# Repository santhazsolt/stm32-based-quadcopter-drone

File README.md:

# STM32-Based Quadcopter Flight Controller

**A custom embedded flight controller built around the STM32F411 microcontroller, an ICM-20948 inertial measurement unit, and a custom-designed PCB.**

This project focuses on the design and development of a quadcopter flight controller, combining embedded C firmware, sensor interfacing, control-system development, power electronics, and printed circuit board (PCB) design.

The goal is to develop a custom hardware and firmware platform capable of reading inertial sensor data, estimating the drone's attitude, processing pilot commands, and controlling four electronic speed controllers (ESCs). The project is also intended to serve as a foundation for future autonomous flight and precision agriculture applications.

**Repository:** [stm32-based-quadcopter-drone](https://github.com/santhazsolt/stm32-based-quadcopter-drone)

---

## Table of Contents

- [Project Overview](#project-overview)
- [Project Objectives](#project-objectives)
- [System Architecture](#system-architecture)
- [Hardware Design](#hardware-design)
- [Power Management](#power-management)
- [Firmware Architecture](#firmware-architecture)
- [Flight Control Fundamentals](#flight-control-fundamentals)
- [Communication Interfaces](#communication-interfaces)
- [Development Tools](#development-tools)
- [Repository Structure](#repository-structure)
- [Development Workflow](#development-workflow)
- [Hardware Bring-Up and Testing](#hardware-bring-up-and-testing)
- [Current Development Status](#current-development-status)
- [Planned Improvements](#planned-improvements)
- [Safety Considerations](#safety-considerations)
- [Learning Outcomes](#learning-outcomes)
- [References](#references)
- [License](#license)

---

## Project Overview

Commercial flight controllers typically integrate a microcontroller, inertial sensors, power regulation, communication interfaces, and motor-control outputs on a single PCB.

This project explores how those components can be designed and integrated into a custom embedded system.

The hardware is built around the **STM32F411CEU6**, an ARM Cortex-M4 microcontroller with an FPU, hardware timers, SPI, UART, ADC, and other peripherals suitable for real-time embedded applications.

The controller interfaces with an **ICM-20948 9-axis IMU**, which combines a 3-axis accelerometer, a 3-axis gyroscope, and a 3-axis magnetometer. The sensor provides measurements that can be used for attitude estimation and flight stabilization.

The project covers two interconnected areas:

- **Hardware:** Schematic design, component selection, PCB layout, power distribution, signal interfacing, and hardware debugging.
- **Firmware:** Peripheral configuration, sensor drivers, inertial data processing, attitude estimation, control algorithms, and ESC signal generation.

The long-term objective is to develop a functional flight-control platform that can be extended with GPS navigation, autonomous flight, and aerial crop-monitoring capabilities.

## Project Objectives

The primary objectives are to:

1. Design a custom flight-controller PCB around the STM32F411.
2. Integrate an inertial measurement unit using SPI communication.
3. Develop embedded C firmware for sensor acquisition and peripheral control.
4. Establish the software architecture for attitude estimation and PID-based stabilization.
5. Generate control signals for four ESCs using STM32 hardware timers.
6. Integrate a radio-control receiver for manual pilot input.
7. Design a power architecture suitable for operation from a LiPo battery.
8. Establish a repeatable hardware bring-up and debugging procedure.
9. Build a modular platform that can support future autonomous navigation and precision agriculture applications.

---

## System Architecture

The flight controller is designed as a real-time embedded system. Its main responsibility is to process sensor measurements and pilot commands, calculate the required control response, and generate motor outputs.

```mermaid
flowchart TD
    BAT[LiPo Battery] --> PWR[Power Management]
    PWR --> MCU[STM32F411]
    PWR --> IMU[ICM-20948 IMU]
    RC[RC Receiver] --> MCU
    IMU -->|SPI| MCU
    MCU -->|PWM or supported ESC protocol| ESC[Four ESCs]
    ESC --> MOT[Four Brushless Motors]
    MCU <--> DBG[SWD Debug Interface]
    MCU <--> USB[USB / Serial Debugging]
    GPS[Future GPS Module] -.-> MCU
```

### Main subsystems

| Subsystem        | Responsibility                                                                |
| ---------------- | ----------------------------------------------------------------------------- |
| STM32F411        | Main processor and real-time control                                          |
| ICM-20948        | Inertial measurements for attitude estimation                                 |
| RC receiver      | Pilot commands and manual control                                             |
| ESC interfaces   | Motor command generation                                                      |
| Power management | Battery input and regulated supply rails                                      |
| SWD interface    | Programming and low-level debugging                                           |
| USB interface    | Development, programming support, or diagnostics, depending on implementation |
| GPS module       | Planned navigation and position estimation                                    |

The architecture separates sensor acquisition, state estimation, control calculations, and actuator output. This separation makes the firmware easier to test, debug, and extend.

---

## Hardware Design

The hardware is being developed in KiCad, from the electrical schematic through PCB layout and manufacturing preparation.

### 1. Microcontroller

**STM32F411CEU6 — ARM Cortex-M4**

The STM32F411 is the central processing unit of the flight controller.

Key capabilities relevant to this project include:

- 32-bit ARM Cortex-M4 core with a floating-point unit.
- Hardware timers for precise timing and PWM generation.
- SPI for high-speed sensor communication.
- UART for serial communication with external modules.
- ADC for analog measurements, including battery-voltage monitoring.
- SWD for programming and debugging.

The exact peripheral allocation, clock configuration, timer assignments, and GPIO mapping are defined by the firmware and hardware design.

### 2. Inertial Measurement Unit

**ICM-20948 — 9-axis IMU**

The ICM-20948 provides:

- 3-axis accelerometer measurements.
- 3-axis gyroscope measurements.
- 3-axis magnetometer measurements.

The accelerometer measures specific force, including the influence of gravity. The gyroscope measures angular velocity. The magnetometer can provide heading-related information when properly calibrated and when magnetic interference is controlled.

The firmware is intended to use these measurements to estimate the drone's orientation.

The sensor communicates with the STM32 through SPI. Because the ICM-20948 has specific digital-I/O voltage requirements, the hardware design incorporates a dedicated 1.8 V supply and logic-level translation between the sensor and the 3.3 V microcontroller domain.

**Important:** Correct sensor identification, register access, initialization, data acquisition, and calibration must be verified on the actual hardware before the IMU can be considered operational.

### 3. Radio-Control Receiver

The controller is designed to accept pilot commands from a radio-control receiver.

The receiver interface is intended to provide the flight controller with inputs such as:

- Roll command.
- Pitch command.
- Yaw command.
- Throttle command.

The receiver protocol and electrical interface must match the selected receiver and firmware configuration. For an IBUS-based receiver, the firmware must correctly configure the appropriate UART, baud rate, packet parsing, and input-validation logic.

Receiver disconnection and invalid or stale commands should be handled explicitly before flight operation.

### 4. ESC and Motor Interfaces

The flight controller is designed to command four ESCs, each driving a brushless DC motor.

The intended quadcopter platform uses:

- Four brushless motors.
- Four ESCs.
- A quadcopter frame.
- A LiPo battery.

The ESC interfaces must use a signal format supported by the selected ESCs and configured in the firmware. PWM is a possible implementation, but the actual timer configuration and signal timings must be verified.

Motor order, rotation direction, and the relationship between motor outputs and the quadcopter's frame orientation must be documented and tested.

### 5. Programming and Debugging

The board is designed to support development and troubleshooting through:

- SWD programming and debugging.
- USB connectivity where supported by the implemented circuit.
- Measurement of regulated power rails.
- Inspection of digital signals with an oscilloscope or logic analyzer.
- Firmware logging and diagnostic output, where implemented.

These interfaces support verification of the power supply, MCU startup, sensor communication, and control-signal generation.

---

## Power Management

Power management is a critical part of the flight-controller design because the system combines a high-current battery-powered propulsion system with low-voltage digital electronics.

The hardware uses a staged power architecture.

| Power stage             | Component                                      | Purpose                                              |
| ----------------------- | ---------------------------------------------- | ---------------------------------------------------- |
| Battery input           | XT60 connector                                 | Main LiPo power connection                           |
| Input protection        | Fuse and reverse-polarity protection circuitry | Protect the input against specified fault conditions |
| Main DC-DC conversion   | TPS54331 buck converter                        | Generate the main regulated supply                   |
| 5 V to 3.3 V            | AMS1117 regulator                              | Supply the MCU and other compatible 3.3 V circuitry  |
| 3.3 V to 1.8 V          | TLV75518 regulator                             | Supply the ICM-20948 digital-I/O voltage domain      |
| Logic-level translation | Dedicated level-shifting circuitry             | Adapt signals between 3.3 V and 1.8 V domains        |

The final electrical behavior depends on the selected component variants, resistor values, capacitor values, PCB implementation, and load conditions.

## Firmware Architecture

The firmware is intended to be organized into independent modules, separating low-level hardware access from flight-control algorithms.

The exact module names and implementation status should follow the source code in the repository.

### 1. Hardware initialization

The initialization layer configures the STM32 peripherals required by the application.

Typical responsibilities include:

- System clock configuration.
- GPIO initialization.
- SPI initialization.
- UART initialization.
- Timer and PWM configuration.
- Interrupt configuration where required.

STM32CubeIDE and STM32CubeMX can be used to configure the device peripherals and generate the initial project configuration.

### 2. IMU driver

The IMU driver is responsible for communication with the ICM-20948.

Its intended responsibilities include:

- Reading the device identification register.
- Resetting and initializing the sensor.
- Configuring accelerometer and gyroscope ranges.
- Configuring the required operating modes.
- Reading sensor registers.
- Converting raw values into engineering units.
- Detecting communication errors.

The SPI interface should be verified independently before sensor-fusion or control algorithms are integrated.

### 3. Sensor calibration and filtering

Raw IMU measurements contain bias, noise, and other errors.

The sensor-processing layer is intended to support:

- Gyroscope bias estimation.
- Accelerometer offset or calibration procedures.
- Conversion from raw measurements to physical units.
- Filtering of noisy measurements.
- Validation of sensor readings.

A complementary filter or a suitable alternative can be used to combine accelerometer and gyroscope data for attitude estimation.

A magnetometer-based heading estimate requires additional calibration and appropriate handling of magnetic interference.

### 4. Attitude estimation

Attitude estimation calculates the orientation of the quadcopter from sensor measurements.

The firmware architecture can accommodate Euler-angle or quaternion-based representations.

The estimated state can provide roll, pitch, and yaw information for the control system. The selected algorithm must account for sensor coordinate conventions, sampling frequency, and numerical stability.

### 5. PID control

PID controllers can be used to reduce the difference between the desired and measured attitude or angular rate.

The general controller equation is:

[
u(t)=K_p e(t)+K_i\int e(t),dt+K_d\frac{de(t)}{dt}
]

where:

- (e(t)) is the control error.
- (K_p) is the proportional gain.
- (K_i) is the integral gain.
- (K_d) is the derivative gain.
- (u(t)) is the controller output.

The actual control architecture may use cascaded rate and attitude loops. Controller execution must use a known timing interval, and the implementation should include appropriate output limits, integral anti-windup, and handling of invalid sensor data.

PID control is a planned or developing subsystem until its implementation and behavior have been verified.

### 6. Motor mixing and output generation

The motor-mixing layer converts control commands into individual motor commands.

For a conventional quadcopter, this combines collective throttle with roll, pitch, and yaw corrections according to the selected frame configuration.

The mixing matrix must match the actual motor numbering, rotation directions, and frame geometry.

The output layer then converts the calculated commands into the electrical signals expected by the ESCs.

### 7. Safety and fault handling

A flight controller must detect conditions that make continued control unsafe.

The firmware should ultimately address:

- Invalid or unavailable IMU data.
- Sensor initialization failures.
- Radio-control signal loss.
- Invalid throttle or control inputs.
- Control-loop timing failures.
- Out-of-range actuator commands.
- Safe startup and motor arming conditions.

These mechanisms must be explicitly implemented and tested. Their presence should not be assumed solely from the firmware architecture.

---

## Flight Control Fundamentals

The intended control pipeline is:

1. Acquire sensor measurements.
2. Validate and calibrate the sensor data.
3. Estimate the vehicle's attitude or angular rate.
4. Decode pilot commands.
5. Calculate the control error.
6. Execute the relevant PID controllers.
7. Apply motor mixing and output limits.
8. Generate ESC signals.
9. Repeat at the configured control-loop rate.

The timing of this pipeline is as important as the individual algorithms. Sensor sampling, controller execution, and actuator updates should be coordinated to provide predictable behavior.

A control-loop frequency should be selected based on sensor configuration, processing requirements, and validated hardware performance rather than assumed in advance.

---

## Communication Interfaces

| Interface          | Intended use                                                              |
| ------------------ | ------------------------------------------------------------------------- |
| SPI                | ICM-20948 communication                                                   |
| UART               | RC receiver or serial peripherals                                         |
| PWM-capable timers | ESC command generation                                                    |
| ADC                | Battery-voltage measurement                                               |
| SWD                | Programming and debugging                                                 |
| USB                | Connectivity and development support, subject to the implemented hardware |

The STM32 peripheral mapping must be documented in the firmware configuration or a dedicated pin-assignment document. Exact pins and alternate functions should not be inferred from the component list alone.

---

## Development Tools

The project uses the following tools and technologies.

| Tool or technology            | Purpose                                          |
| ----------------------------- | ------------------------------------------------ |
| KiCad                         | Schematic capture and PCB design                 |
| STM32CubeIDE                  | Firmware development, compilation, and debugging |
| STM32CubeMX                   | Peripheral and clock configuration               |
| STM32CubeProgrammer           | Programming and device access                    |
| ST-LINK                       | SWD debugging and flashing                       |
| C                             | Embedded firmware development                    |
| Oscilloscope / logic analyzer | Hardware signal inspection                       |
| Git and GitHub                | Version control and project documentation        |

Relevant embedded topics include SPI, UART, ADC, timer configuration, PWM generation, sensor calibration, real-time control, and hardware debugging.

## Development Workflow

The project follows a hardware-and-firmware development process.

### Hardware development

1. Define system requirements and component interfaces.
2. Select the microcontroller, IMU, power components, connectors, and protection circuitry.
3. Design the electrical schematic in KiCad.
4. Perform electrical-rule checks and manually review critical circuits.
5. Assign and verify component footprints.
6. Transfer the schematic to the PCB editor.
7. Define the board outline, mounting holes, and connector locations.
8. Place components and route the PCB.
9. Perform design-rule checks and review manufacturing outputs.
10. Manufacture and assemble the PCB.
11. Bring up the board progressively, checking each supply rail and subsystem.

### Firmware development

1. Configure the STM32 clocks and peripherals.
2. Verify startup, programming, and debugging.
3. Test the SPI communication interface.
4. Implement and validate IMU initialization and data acquisition.
5. Verify calibration and sensor-data conversion.
6. Develop and test the attitude-estimation algorithm.
7. Implement control-loop timing and PID calculations.
8. Verify motor mixing and ESC signal generation without propellers.
9. Integrate the receiver and validate input handling.
10. Perform staged, controlled system testing.

---

## Planned Improvements

### Flight-control functionality

- Complete the IMU driver and sensor calibration.
- Implement and validate attitude estimation.
- Develop PID-based rate and attitude control.
- Add motor mixing and output constraints.
- Implement arming logic and failsafe behavior.
- Improve diagnostics and runtime fault detection.

### Hardware validation

- Complete PCB manufacturing and assembly.
- Validate power integrity and signal levels.
- Measure sensor communication timing.
- Verify ESC interfaces and receiver compatibility.
- Document hardware revisions and any required design changes.

### Autonomous navigation

Future development may include:

- GPS integration.
- Position and altitude estimation using suitable additional sensors.
- Return-to-Home functionality.
- Autonomous waypoint navigation.
- Telemetry and mission monitoring.

These capabilities require additional hardware, algorithms, and extensive validation beyond basic attitude stabilization.

### Precision agriculture

An additional long-term objective is to use the quadcopter as a platform for agricultural monitoring.

Potential applications include:

- Aerial field mapping.
- Multispectral image acquisition.
- Vegetation-index calculations such as NDVI.
- Crop-health monitoring.
- Integration with a companion computer for image processing and autonomous mission planning.

These are future extensions rather than assumed capabilities of the current flight controller.

---

## Learning Outcomes

This project provides practical experience in:

- Embedded C development on STM32 microcontrollers.
- Peripheral configuration and real-time firmware architecture.
- SPI communication with inertial sensors.
- PCB schematic capture, layout, and design verification.
- Power regulation and signal-level compatibility.
- ADC measurements and sensor-data processing.
- Attitude estimation and feedback-control fundamentals.
- Timer-based actuator control.
- Hardware debugging using SWD and laboratory instruments.
- System integration across hardware, firmware, and control algorithms.

The project combines electronics engineering and embedded software development in a single system, with a focus on understanding the interactions between physical hardware and real-time control.

---

## References

- [STM32F411 documentation — STMicroelectronics](https://www.st.com/en/microcontrollers-microprocessors/stm32f411/documentation.html)
- [STM32F411 datasheet — STMicroelectronics](https://www.st.com/resource/en/datasheet/stm32f411ce.pdf)
- [KiCad documentation](https://docs.kicad.org/)
- [STM32CubeIDE — STMicroelectronics](https://www.st.com/en/development-tools/stm32cubeide.html)
- [ICM-20948 product documentation — TDK InvenSense](https://invensense.tdk.com/products/motion-tracking/9-axis/icm-20948/)

Consult the applicable datasheets and reference manuals for the exact device variants used in the hardware.

---

## License

Specify the project's license here once it has been selected. If the repository includes both firmware and hardware design files, make sure the chosen license covers the intended reuse of each type of artifact.

---

**Author:** Zsolt Sántha

**Project:** STM32-Based Quadcopter Flight Controller

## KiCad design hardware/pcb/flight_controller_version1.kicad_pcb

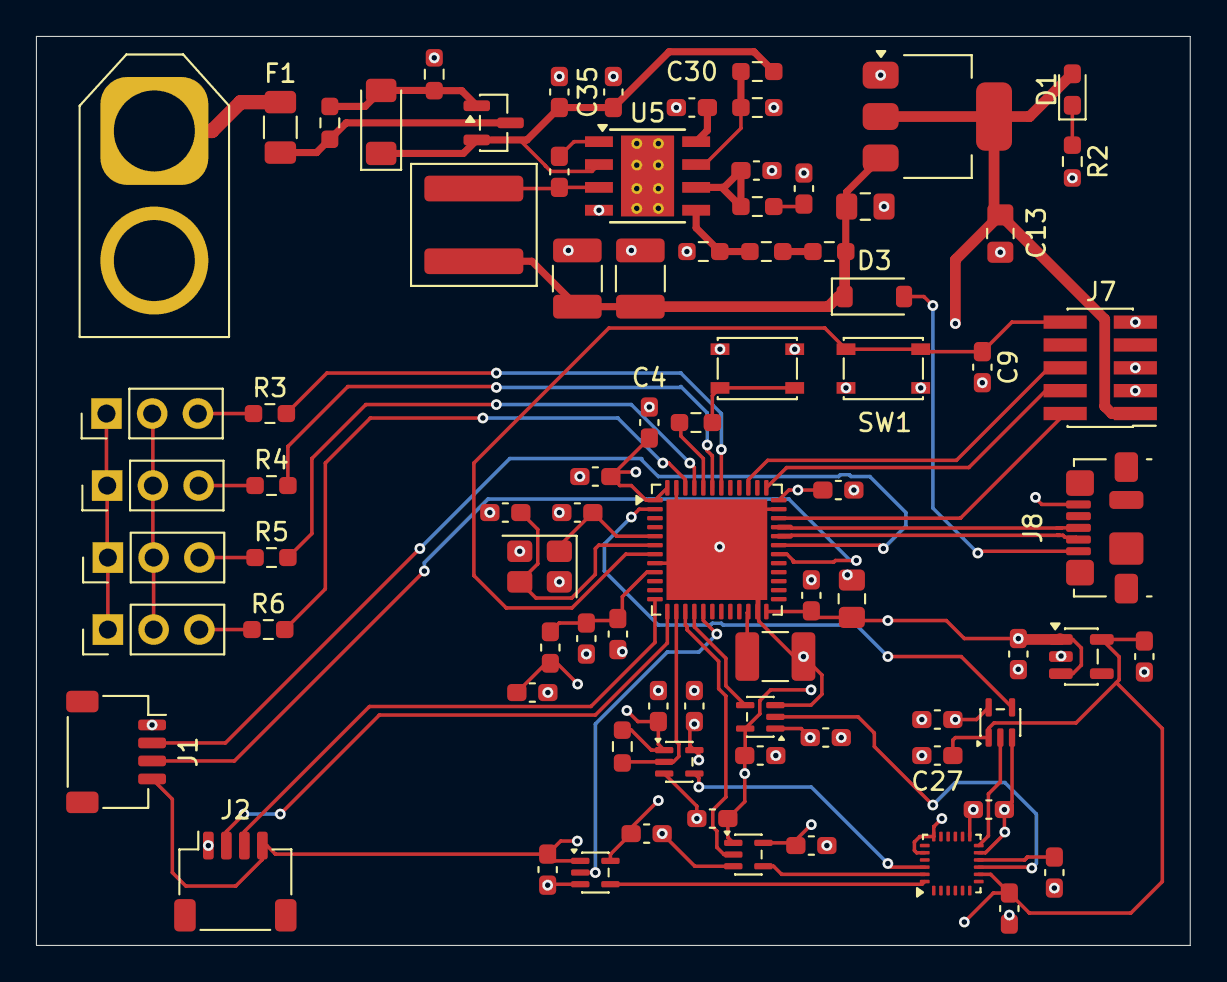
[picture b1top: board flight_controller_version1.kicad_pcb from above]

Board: 4 copper layers, 64.1 x 50.5 mm, 81 parts (0 on the bottom side), 54 nets.

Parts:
C1, C2, C3, C4, C6, C9: 100n; C_0603_1608Metric_Pad1.08x0.95mm_HandSolder
C5: 10u; C_0805_2012Metric_Pad1.18x1.45mm_HandSolder
C7, C8, C17, C18: 1u; C_0603_1608Metric_Pad1.08x0.95mm_HandSolder
C10, C11: 10p; C_0603_1608Metric_Pad1.08x0.95mm_HandSolder
C12, C13: 22u; C_0805_2012Metric_Pad1.18x1.45mm_HandSolder
C14, C15, C16, C19, C20, C21, C22, C23, C24, C25, C26, C27, C28, C29: 0.1u; C_0603_1608Metric_Pad1.08x0.95mm_HandSolder
C30, C33: 0.1 u; C_0603_1608Metric_Pad1.08x0.95mm_HandSolder
C31: 120p; C_0603_1608Metric_Pad1.08x0.95mm_HandSolder
C32: 12n; C_0603_1608Metric_Pad1.08x0.95mm_HandSolder
C34, C36: 47u; C_1210_3225Metric_Pad1.33x2.70mm_HandSolder
C35: 10u; C_0603_1608Metric_Pad1.08x0.95mm_HandSolder
C37: 4.7u; C_1210_3225Metric_Pad1.33x2.70mm_HandSolder
D1: RED; LED_0603_1608Metric_Pad1.05x0.95mm_HandSolder
D3: D_Schottky; D_SOD-123
D4: BZV55B10; D_MiniMELF
F1: Fuse; Fuse_1206_3216Metric
FB1: 120R; L_0603_1608Metric_Pad1.05x0.95mm_HandSolder
J1, J2: Conn_01x04_Pin; JST_SH_SM04B-SRSS-TB_1x04-1MP_P1.00mm_Horizontal
J3, J4, J5, J6: Conn_01x03_Pin; PinHeader_1x03_P2.54mm_Vertical
J7: Conn_ARM_JTAG_SWD_10; PinHeader_2x05_P1.27mm_Vertical_SMD
J8: USB_B_Micro; USB_Micro-B_Molex_47346-0001
J9: XT60-Bat; AMASS_XT60-M_1x02_P7.20mm_Vertical
L1: 15 u; L_Coilcraft_XAL6060-XXX
Q2: AO3401A; SOT-23
R1, R16: 10k; R_0603_1608Metric_Pad0.98x0.95mm_HandSolder
R2: 1k5; R_0603_1608Metric_Pad0.98x0.95mm_HandSolder
R3, R4, R5, R6: 22; R_0603_1608Metric_Pad0.98x0.95mm_HandSolder
R8: 3.75k; R_0603_1608Metric_Pad0.98x0.95mm_HandSolder
R9: 19k; R_0603_1608Metric_Pad0.98x0.95mm_HandSolder
R10: 51; R_0603_1608Metric_Pad0.98x0.95mm_HandSolder
R11: 374k; R_0603_1608Metric_Pad0.98x0.95mm_HandSolder
R12: 61.9k; R_0603_1608Metric_Pad0.98x0.95mm_HandSolder
R13, R14: 100k; R_0603_1608Metric_Pad0.98x0.95mm_HandSolder
R15: 22k; R_0603_1608Metric_Pad0.98x0.95mm_HandSolder
SW1: SW_Push_Open; SW_SPST_PTS810
SW_BOOT1: SW_SPDT; SW_SPST_PTS810
U1: STM32F411CEUx; QFN-48-1EP_7x7mm_P0.5mm_EP5.6x5.6mm
U2: ICM-20948; InvenSense_QFN-24_3x3mm_P0.4mm
U3: AMS1117-3.3; SOT-223-3_TabPin2
U4: TLV75518PDBV; SOT-23-5
U5: TPS54336ADDA; TI_SO-PowerPAD-8_ThermalVias
U6, U7, U8, U9, U10: SN74AUP1T34DCK; SOT-353_SC-70-5
Y1: 16MHz; Crystal_SMD_3225-4Pin_3.2x2.5mm

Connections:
+1.8V: C16.1, C17.1, C21.1, C22.1, C24.1, C25.1, C27.1, U2.8 (VDDIO), U4.5 (OUT), U6.5 (VCCB), U7.1 (VCCA), U8.1 (VCCA), U9.5 (VCCB), U10.5 (VCCB)
+3.3V: C1.1, C2.1, C3.1, C4.1, C5.1, C8.1, C13.1, C14.1, C18.1, C19.1, C20.1, C23.1, C26.1, C28.1, D1.2 (A), FB1.2, J1.4, J2.4, J7.1 (VTref), R16.1, U1.1 (VBAT), U1.24 (VDD), U1.36 (VDD), U1.48 (VDD), U2.13 (VDD), U3.2 (VO), U4.1 (IN), U4.3 (EN), U6.1 (VCCA), U7.5 (VCCB), U8.5 (VCCB), U9.1 (VCCA), U10.1 (VCCA)
+3.3VA: C6.1, C7.1, FB1.1, U1.9 (VDDA)
+5V: J3.2, J4.2, J5.2, J6.2
/STM32F411CEUx2 (page 2)/PWR_LED_K: D1.1 (K), R2.1
/STM32F411CEUx/HSE_IN: C10.1, U1.5 (PH0), Y1.1
/STM32F411CEUx/HSE_OUT: C11.1, U1.6 (PH1), Y1.3
GND: C1.2, C2.2, C3.2, C4.2, C5.2, C6.2, C7.2, C8.2, C9.2, C10.2, C11.2, C12.2, C13.2, C14.2, C15.2, C16.2, C17.2, C18.2, C19.2, C20.2, C21.2, C22.2, C23.2, C24.2, C25.2, C26.2, C27.2, C28.2, C29.2, C30.2, C31.2, C32.1, C34.1, C35.2, C36.1, C37.2, J1.1, J2.1, J3.1, J4.1, J5.1, J6.1, J7.3 (GND), J7.5 (GND), J7.9 (GNDDetect), J8.5 (GND), J9.2, R2.2, R9.1, R12.2, R15.2, SW1.1 (A), SW_BOOT1.1 (A), U1.8 (VSSA), U1.23 (VSS), U1.35 (VSS), U1.47 (VSS), U1.49 (VSS), U2.11 (FSYNC), U2.18 (GND), U2.20 (GND), U3.1 (GND), U4.2 (GND), U5.4 (GND), U5.9 (ETPAD), U6.3 (GND), U7.3 (GND), U8.3 (GND), U9.3 (GND), U10.3 (GND), Y1.2 (G), Y1.4 (G)
IMU_INT_ICM: U2.12 (INT1), U8.2 (A)
IMU_INT_STM: U1.2 (PC13), U8.4 (B)
NRST: C9.1, J7.10 (~RESET), SW1.2 (B), U1.7 (NRST)
unnamed: C32.2, R8.2
unnamed: C12.1, C34.2, C36.2, D3.1 (K), L1.2, R10.1, U3.3 (VI)
unnamed: D4.2 (A), Q2.1 (G), R14.2, R15.1
unnamed: C29.1, C35.1, D4.1 (K), Q2.2 (S), R11.1, U5.2 (VIN)
unnamed: F1.1, J9.1
unnamed: F1.2, Q2.3 (D), R14.1
unnamed: R10.2, R13.1
unnamed: R1.1, SW_BOOT1.2 (B)
unnamed: R1.2, U1.44 (BOOT0)
unnamed: R3.2, U1.42 (PB6)
unnamed: R4.2, U1.43 (PB7)
unnamed: R5.2, U1.45 (PB8)
unnamed: R6.2, U1.46 (PB9)
unnamed: C37.1, U1.22 (VCAP1)
unnamed: C15.1, U2.10 (REGOUT)
unnamed: C33.1, U5.1 (BOOT)
unnamed: C31.1, R8.1, U5.6 (COMP)
unnamed: C33.2, L1.1, U5.3 (PH)
unnamed: C30.1, U5.8 (SS)
unnamed: R9.2, R13.2, U5.5 (VSENSE)
PWM_1: J3.3, R3.1
PWM_2: J4.3, R4.1
PWM_3: J5.3, R5.1
PWM_4: J6.3, R6.1
SPI1_CS: R16.2, U1.14 (PA4), U6.2 (A)
SPI1_MISO: U1.16 (PA6), U7.4 (B)
SPI1_MOSI: U1.17 (PA7), U9.2 (A)
SPI1_NCS: U2.22 (~CS), U6.4 (B)
SPI1_SCK: U1.15 (PA5), U10.2 (A)
SPI1_SCLK: U2.23 (SCL/SCLK), U10.4 (B)
SPI1_SDI: U2.24 (SDA/SDI), U9.4 (B)
SPI1_SDO: U2.9 (SDO/AD0), U7.2 (A)
SWCLK: J7.4 (SWCLK/TCK), U1.37 (PA14)
SWDIO: J7.2 (SWDIO/TMS), U1.34 (PA13)
SWO: J7.6 (SWO/TDO), U1.39 (PB3)
USART1_RX: J1.2, U1.31 (PA10)
USART1_TX: J1.3, U1.30 (PA9)
USART2_RX: J2.2, U1.13 (PA3)
USART2_TX: J2.3, U1.12 (PA2)
USB_D+: J8.3 (D+), U1.33 (PA12)
USB_D-: J8.2 (D-), U1.32 (PA11)
USB_VBUS: D3.2 (A), J8.1 (VBUS)
V_EN: R11.2, R12.1, U5.7 (EN)

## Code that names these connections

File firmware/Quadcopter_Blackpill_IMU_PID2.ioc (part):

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PA6.GPIOParameters=GPIO_Label
PA6.Mode=Full_Duplex_Master
PA7.Mode=Full_Duplex_Master
Mcu.UserName=STM32F411CEUx
PA9.GPIO_Label=M2_PWM
PA9.GPIOParameters=GPIO_Label
PA11.GPIOParameters=GPIO_Label
PA11.GPIO_Label=M4_PWM
PA6.GPIO_Label=SPI_MISO
RCC.SYSCLKSource=RCC_SYSCLKSOURCE_PLLCLK
PA13.Signal=SYS_JTMS-SWDIO
PA3.Mode=Asynchronous
PA8.GPIO_Label=M1_PWM
PA9.Signal=S_TIM1_CH2
PA8.GPIOParameters=GPIO_Label
PA5.Signal=SPI1_SCK
RCC.HSE_VALUE=25000000
board=custom
PA14.Mode=Serial_Wire
PA10.GPIO_Label=M3_PWM
PA10.GPIOParameters=GPIO_Label
PA8.Signal=S_TIM1_CH1
PA4.GPIOParameters=GPIO_Label
PA13.Mode=Serial_Wire
Mcu.Name=STM32F411C(C-E)Ux
PA2.Signal=USART2_TX
PA4.Signal=GPIO_Output
RCC.SYSCLKFreq_VALUE=96000000
Mcu.Package=UFQFPN48
PA6.Signal=SPI1_MISO
PA7.GPIO_Label=SPI_MOSI
PA11.Signal=S_TIM1_CH4
PA10.Signal=S_TIM1_CH3
PA14.Signal=SYS_JTCK-SWCLK
PA2.Mode=Asynchronous
PA4.GPIO_Label=SPI_CS
PA7.GPIOParameters=GPIO_Label
PA3.Signal=USART2_RX
PA5.Mode=Full_Duplex_Master
PA7.Signal=SPI1_MOSI
